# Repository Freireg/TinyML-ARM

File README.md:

# TinyML-ARM
# Overview
This is my personal repository to test test TinyML Applications in ARM Cortex-M devices.
> * This branch model:  Sine Wave
> * Plataform used:     STM32F407 | CUBE IDE
> * Current status:     Working!
# Machine Learning Model
The modeling process can be found on [TinyML_Example_Model](https://github.com/Freireg/TinyML-ESP32/blob/main/TinyML_ESP32_Example.ipynb).
# Firmware Implementation
This is a common example that uses neural networks to figure the output of a sine wave.
Training the model and the use of the Tensorflow Lite library are based on TinyML guide, STM32 specificities and building process base on [Shawn Hymel guide](https://www.digikey.com/en/maker/projects/tinyml-getting-started-with-tensorflow-lite-for-microcontrollers/c0cdd850f5004b098d263400aa294023).

> Important note: The tensorflow related files are in the folder **/Core/Support-files**. Those are the files which describes how to setup and run the inference based on the application necessities.
```
Supported-files
├── Inc
│   ├── constants.h
│   ├── main_functions.h
│   ├── model.h
│   └── output_handler.h
└── Src
    ├── constants.cpp
    ├── main_functions.cpp
    ├── model.cpp
    └── output_handler.cpp

```

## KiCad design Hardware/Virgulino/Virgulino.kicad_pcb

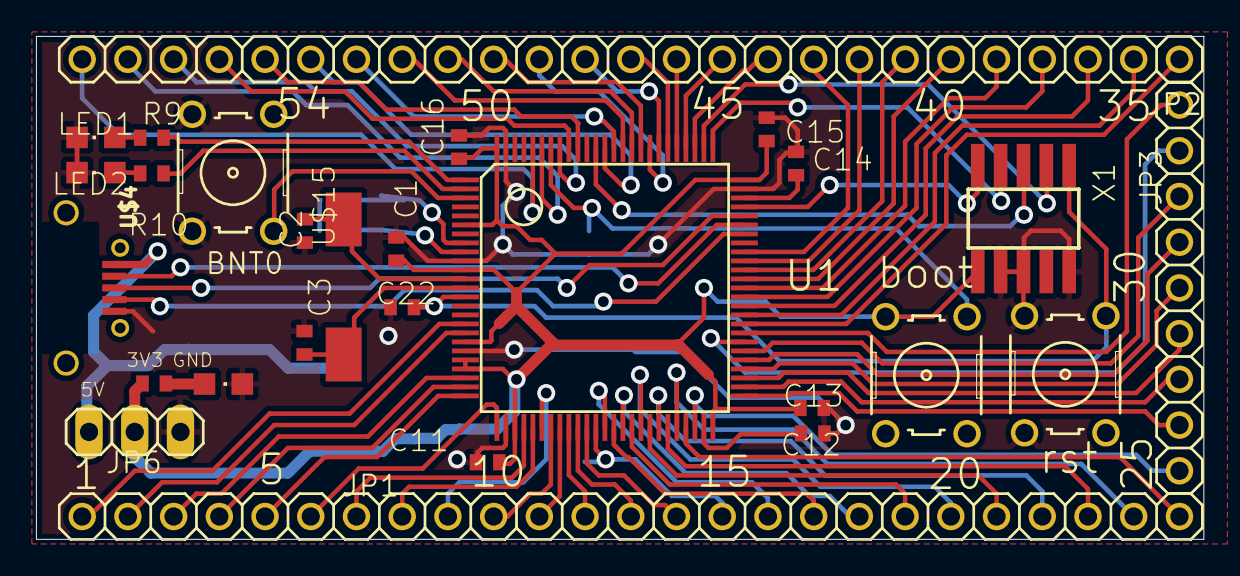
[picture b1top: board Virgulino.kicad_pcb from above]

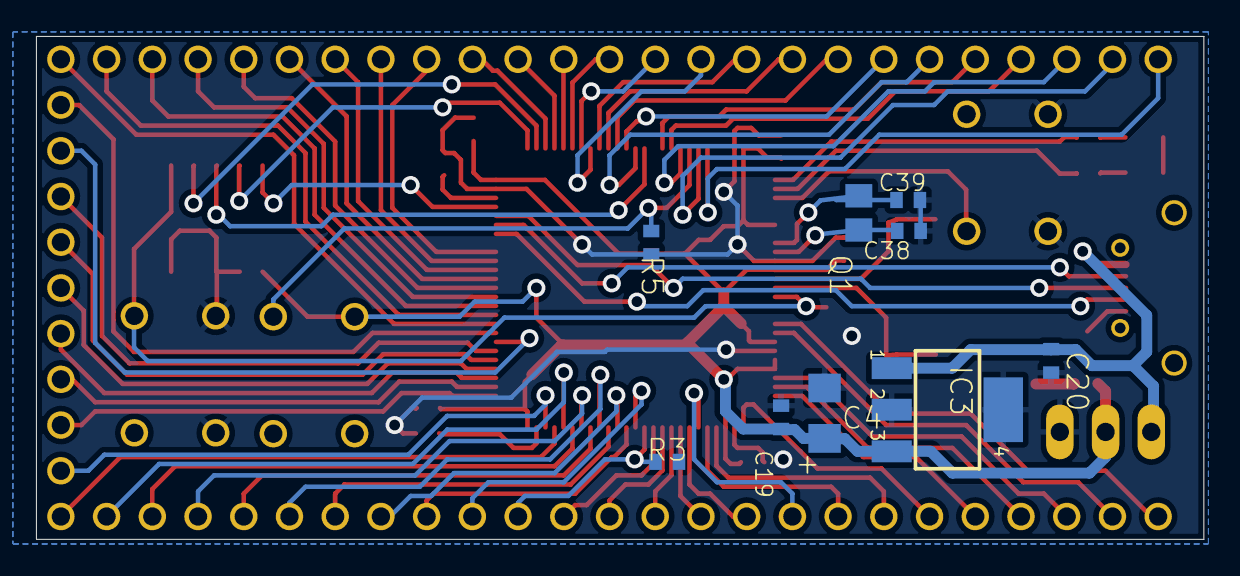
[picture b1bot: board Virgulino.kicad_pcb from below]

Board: 4 copper layers, 64.9 x 27.9 mm, 36 parts (9 on the bottom side), 83 nets.

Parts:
BNT0: B3F-F05XX
C1: 100 nF; C0402
C2, C3: 12pF; C0402
C4: 10uF; CPOL1206
C11, C13, C15, C16, C19, C20: 100nF; C0402
C12, C14: 2uF; C0402
C22: 10nF; C0402
C38, C39: 22pF; C0402
IC3: MIC5209-3.3YS; SOT223
JP1, JP2: 1X25_ROUND
JP3: 1X09_ROUND
JP6: 1X03
LED1, LED2: CHIPLED_0805
PWR0: CHIPLED_0805
Q1: 32.768KHz; 0805
R3, R5: 100k; R0402
R8, R9, R10: 0; R0402
RESET0, RESET1: B3F-F05XX
U1: TQFP100
U$4: ZX62D
U$15: 12MHz; CSM-3X
X1: 1365-10

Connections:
5V: C20.1, IC3.1, JP6.1, U$4.P$1
+3V3: C1.1, C4.+, C11.1, C13.1, C15.1, C16.1, C19.1, IC3.3, JP6.2, R8.2, RESET1.1, RESET1.2, U1.6, U1.11, U1.19, U1.21, U1.22, U1.28, U1.50, U1.75, U1.100, X1.10
BNT: BNT0.1, BNT0.2, U1.3
GND: BNT0.3, BNT0.4, C1.2, C2.2, C3.2, C4.-, C11.2, C12.2, C13.2, C14.2, C15.2, C16.2, C19.2, C20.2, C22.2, C38.2, C39.2, IC3.2, IC3.4, JP6.3, LED1.C, LED2.C, PWR0.C, R3.1, R5.1, RESET0.3, RESET0.4, U1.10, U1.20, U1.27, U1.74, U1.99, U$4.P$5, X1.2, X1.6, X1.8
ID: U1.69, U$4.P$4
JTCK: U1.76, X1.7
JTDI: U1.77, X1.3
JTDO: U1.89, X1.5
JTMS: U1.72, X1.9
LED1: R9.2, U1.1
LED2: R10.2, U1.2
unnamed: C3.1, U1.13, U$15.2
unnamed: C2.1, U1.12, U$15.1
unnamed: C12.1, U1.49
unnamed: C14.1, U1.73
unnamed: R5.2, RESET1.3, RESET1.4, U1.94
unnamed: PWR0.A, R8.1
unnamed: LED1.A, R9.1
unnamed: LED2.A, R10.1
unnamed: C38.1, Q1.1, U1.9
unnamed: C39.1, Q1.2, U1.8
NRST: C22.1, RESET0.1, RESET0.2, U1.14, X1.1
PA0: JP1.3, U1.23
PA1: JP1.4, U1.24
PA2: JP1.5, U1.25
PA3: JP1.6, U1.26
PA4: JP1.7, U1.29
PA5: JP1.8, U1.30
PA6: JP1.9, U1.31
PA7: JP1.10, U1.32
PA8: JP2.9, U1.67
PB0: JP1.13, U1.35
PB1: JP1.14, U1.36
PB2: JP1.15, R3.2, U1.37
PB5: JP2.21, U1.91
PB6: JP2.22, U1.92
PB7: JP2.23, U1.93
PB8: JP2.24, U1.95
PB9: JP2.25, U1.96
PB10: JP1.25, U1.47
PB11: JP3.1, U1.48
PB12: JP3.2, U1.51
PB13: JP3.3, U1.52
PB14: JP3.4, U1.53
PB15: JP3.5, U1.54
PC2: JP1.1, U1.17
PC3: JP1.2, U1.18
PC4: JP1.11, U1.33
PC5: JP1.12, U1.34
PC6: JP2.5, U1.63
PC7: JP2.6, U1.64
PC8: JP2.7, U1.65
PC9: JP2.8, U1.66
PC10: JP2.10, U1.78
PC11: JP2.11, U1.79
PC12: JP2.12, U1.80
PD0: JP2.13, U1.81
PD1: JP2.14, U1.82
PD2: JP2.15, U1.83
PD3: JP2.16, U1.84
PD4: JP2.17, U1.85
PD5: JP2.18, U1.86
PD6: JP2.19, U1.87
PD7: JP2.20, U1.88
PD8: JP3.6, U1.55
PD9: JP3.7, U1.56
PD10: JP3.8, U1.57
PD11: JP3.9, U1.58
PD12: JP2.1, U1.59
PD13: JP2.2, U1.60
PD14: JP2.3, U1.61
PD15: JP2.4, U1.62
PE7: JP1.16, U1.38
PE8: JP1.17, U1.39
PE9: JP1.18, U1.40
PE10: JP1.19, U1.41
PE11: JP1.20, U1.42
PE12: JP1.21, U1.43
PE13: JP1.22, U1.44
PE14: JP1.23, U1.45
PE15: JP1.24, U1.46
USB_D_N: U1.70, U$4.P$2
USB_D_P: U1.71, U$4.P$3

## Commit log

2022-09-30 [Firmware] Sine Wave model working
2022-09-30 GitIgnore File
2022-09-30 GitIgnore changes
2022-09-30 Deleting vuild files
2022-09-30 Repo Organization
2022-09-30 Minor repo changes
2022-10-02 [Firmware] SineWave model fully working
2022-10-02 [README] Changes
